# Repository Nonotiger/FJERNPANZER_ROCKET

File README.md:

# FJERNPANZER_ROCKET
This is theoretical design of a rocket produced by FJERNPANZER. The rocket will be converted into a military applicance, if rocket fuel is acquired.

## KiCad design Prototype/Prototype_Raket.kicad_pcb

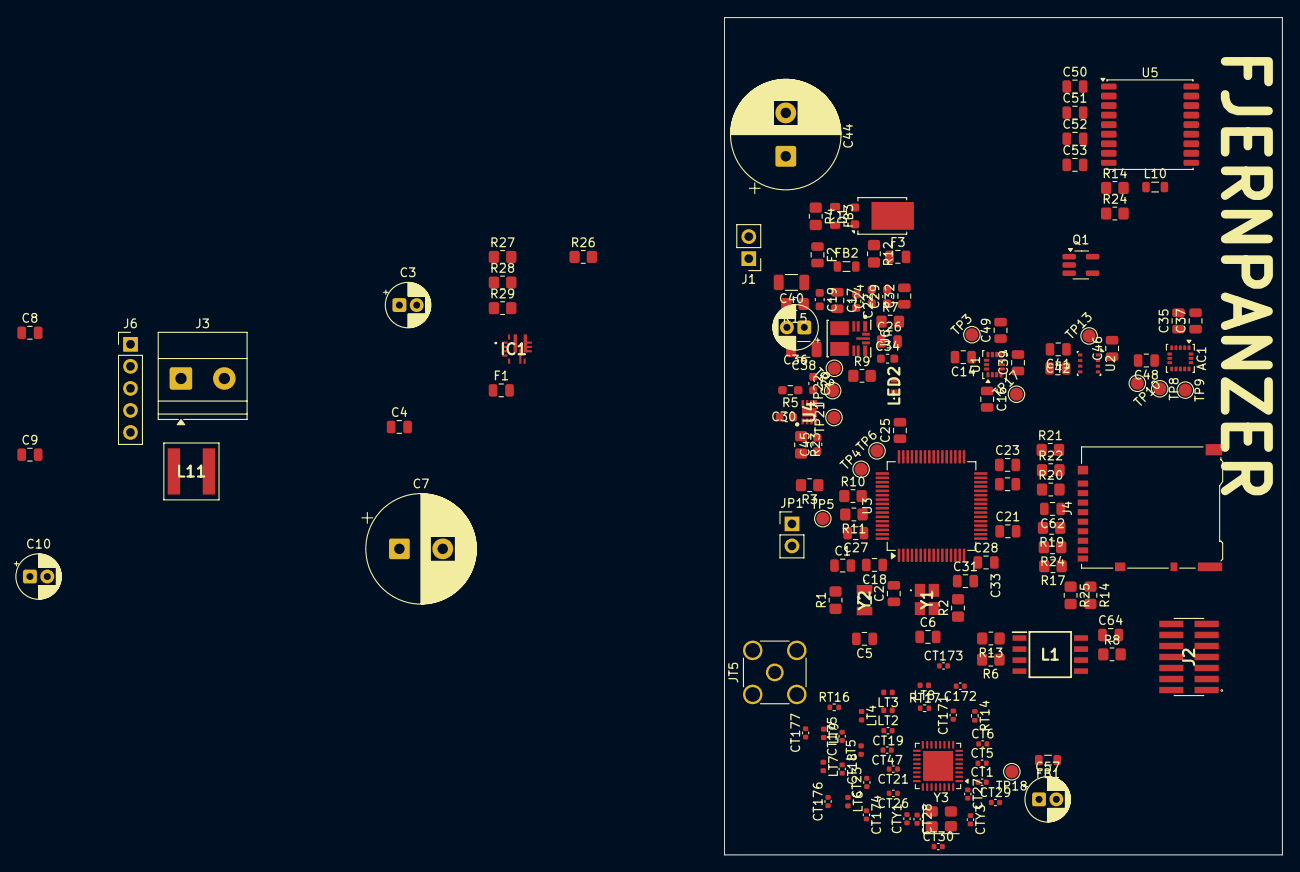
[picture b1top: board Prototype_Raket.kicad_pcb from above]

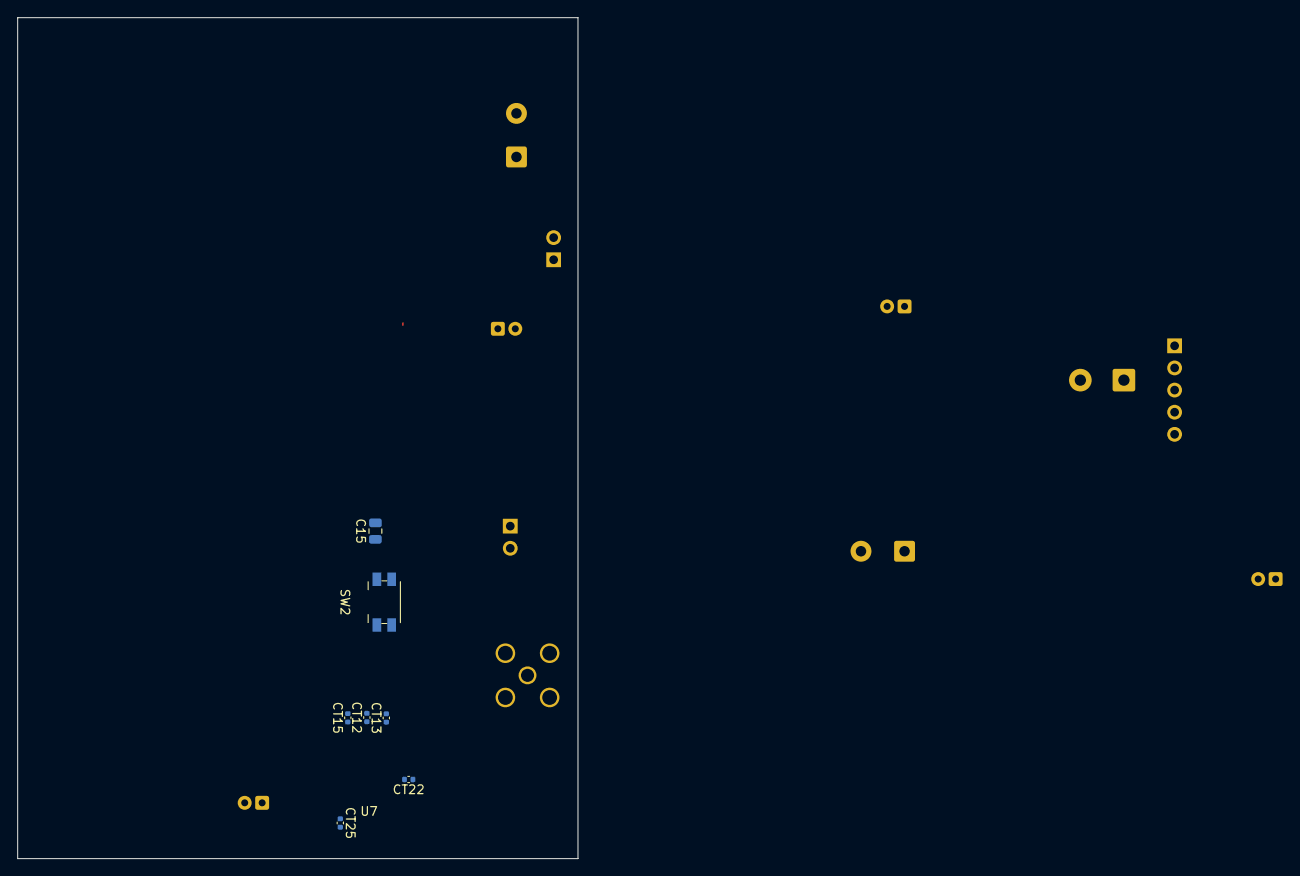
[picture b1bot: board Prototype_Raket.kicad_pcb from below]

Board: 4 copper layers, 64.3 x 96.5 mm, 163 parts (7 on the bottom side), 95 nets.

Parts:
AC1: H3LIS331DLTR; LGA-16_3x3mm_P0.5mm_LayoutBorder3x5y
C1, C5: C_0805_2012Metric
C2, C6: 16p; C_0805_2012Metric
C3: 15uF; CP_Radial_D5.0mm_P2.00mm
C4, C8, C62, C64: 100nF; C_0805_2012Metric
C7, C44: 1000uF; CP_Radial_D12.5mm_P5.00mm
C9: 100pF; C_0805_2012Metric
C10, C57: 47uF; CP_Radial_D5.0mm_P2.00mm
C14, C15, C16, C21, C23, C25, C27, C32, C37, C39, C41, C42, C46, C48, C49, C50, C51, C52, C53: 100n; C_0805_2012Metric
C17: 10u; C_0805_2012Metric
C18, C33: 4u7; C_0805_2012Metric
C19, C20, C30, C45: 100n; C_0603_1608Metric
C22, C24: 2u2; C_0603_1608Metric
C26: 100u; C_0805_2012Metric
C28: 1u; C_0805_2012Metric
C29: 4u7; C_0603_1608Metric
C31: 10n; C_0805_2012Metric
C34: 1u; C_0603_1608Metric
C35: 10uF; C_0805_2012Metric
C36: 22u; CP_Radial_D5.0mm_P2.00mm
C38, C40: 22u; C_1206_3216Metric
C172: 100pF; C_0402_1005Metric
CT1, CT5, CT12, CT13, CT15, CT22, CT25, CT26, CT27, CT28, CT29: 47nF; C_0402_1005Metric
CT6: 220nF; C_0402_1005Metric
CT18: 2.2pF; C_0402_1005Metric
CT19, CT47: 3.3pF; C_0402_1005Metric
CT21, CT171: 10nF; C_0402_1005Metric
CT23: 1.5nF; C_0402_1005Metric
CT30, CT177: DNM_0402; C_0402_1005Metric
CT173: 33pF; C_0402_1005Metric
CT174: 15pF; C_0402_1005Metric
CT175: 3pF; C_0402_1005Metric
CT176: 1pF; C_0402_1005Metric
CTY1, CTY3: 15pF; C_0402_1005Metric
D1: Not Decided; TO-277B
F1, F2, F3: Not Decided; C_0805_2012Metric
FB1: BLM18KG102BH1D; L_0805_2012Metric
FB2: BMC-Q1J0005H; L_0805_2012Metric
FB3: 600R@100MHz; L_0805_2012Metric
IC1: TPS56637RPAR
J1: Conn_01x02_Pin; PinHeader_1x02_P2.54mm_Vertical
J2: FTSH-107-01-F-DV-K; FTSH-107-XX-YYY-DV-K
J3: Conn_01x02_Pin; TerminalBlock_Phoenix_MKDS-1,5-2_1x02_P5.00mm_Horizontal
J4: Micro_SD_Card_Det_Hirose_DM3AT; microSD_HC_Hirose_DM3AT-SF-PEJM5
J6: Conn_01x05_Pin; PinHeader_1x05_P2.54mm_Vertical
JP1: Jumper_2_Small_Open; PinHeader_1x02_P2.54mm_Vertical
JT5: W5017; SMA_Amphenol_132291_Vertical
L1: W25Q128JVSIQ_TR; SOIC127P780X195-8N
L10: L_Small; L_0805_2012Metric
L11: 5.6uH, 14.5mOhm; XAL6060562MEC
LED2: VLMTG1400-GS08; VLMTG1400GS08
LT2: 15nH; L_0402_1005Metric
LT3, LT4, LT5, LT9: 12nH; L_0402_1005Metric
LT6: 7.5nH; L_0402_1005Metric
LT7: 18nH; L_0402_1005Metric
LT8: 10nH; L_0402_1005Metric
Q1: PMOS; SOT-23-5_HandSoldering
R1, R2, R7: 0R; R_0805_2012Metric_Pad1.20x1.40mm_HandSolder
R3, R12, R13, R14, R24#2, R25, R26, R29: 10k; R_0805_2012Metric_Pad1.20x1.40mm_HandSolder
R4: 3.3m; R_0805_2012Metric_Pad1.20x1.40mm_HandSolder
R5: 1k5; R_0603_1608Metric_Pad0.98x0.95mm_HandSolder
R6, R8, R10, R11: 4k7; R_0805_2012Metric_Pad1.20x1.40mm_HandSolder
R9: 510R; R_0805_2012Metric_Pad1.20x1.40mm_HandSolder
R14#2: 56k; R_0805_2012Metric_Pad1.20x1.40mm_HandSolder
R15: 10m; R_0805_2012Metric_Pad1.20x1.40mm_HandSolder
R17, R19, R20, R21, R22: 47k; R_0805_2012Metric_Pad1.20x1.40mm_HandSolder
R23: 1k5; R_0805_2012Metric_Pad1.20x1.40mm_HandSolder
R24: 10; R_0805_2012Metric_Pad1.20x1.40mm_HandSolder
R27: 20k; R_0805_2012Metric_Pad1.20x1.40mm_HandSolder
R28: 73k; R_0805_2012Metric_Pad1.20x1.40mm_HandSolder
RT14: 56k; R_0402_1005Metric
RT16: 10m; R_0402_1005Metric
RT17: 10; R_0402_1005Metric
SW2: SW_Push; Panasonic_EVQPUJ_EVQPUA
TP2, TP3, TP4, TP5, TP6, TP8, TP9, TP10, TP13, TP17, TP18, TP21, TP22: TestPoint; TestPoint_Pad_D1.5mm
U1: ISM330DLC; LGA-14_3x2.5mm_P0.5mm_LayoutBorder3x4y
U2: BME280; Bosch_LGA-8_2.5x2.5mm_P0.65mm_ClockwisePinNumbering
U3: STM32F446RETx; LQFP-64_10x10mm_P0.5mm
U4: INA2180A3IDSGR; SON50P200X200X80-9N
U5: MAX-M10S; ublox_MAX
U6: TPSM33620S3QRDNRQ1
U7: CC1200; QFN-32-1EP_5x5mm_P0.5mm_EP3.45x3.45mm
Y1: FL2400135Z
Y2: SC32A-9PF10PPM; SC32A9PF10PPM
Y3: CS03880-40M; Crystal_SMD_3225-4Pin_3.2x2.5mm

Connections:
+3.3V: AC1.1 (VDD_IO), AC1.7 (SDO_SA0), AC1.8 (CS), AC1.14 (VDD), AC1.15 (RESERVED_2), C14.1, C16.1, C18.1, C20.2, C21.1, C23.1, C25.1, C27.1, C28.1, C31.1, C35.1, C37.1, C39.1, C40.1, C41.1, C42.1, C46.1, C48.1, C49.1, C50.1, C51.1, C62.1, C64.1, FB1.1, J4.4 (VDD), JP1.2 (B), L1.8 (VCC), Q1.2 (G), Q1.3 (S), R6.2, R8.2, R9.1, R10.1, R11.2, R12.1, R13.2, R14.2, R15.2, R17.2, R19.2, R20.1, R21.1, R22.1, R24#2.2, R25.2, R26.1, TP3.1 (1_1), TP6.1 (1_1), TP10.1 (1_1), TP13.1 (1_1), U1.1 (SDO/SA0), U1.5 (VDDIO), U1.8 (VDD), U1.12 (CS), U2.2 (CSB), U2.6 (VDDIO), U2.8 (VDD), U3.1 (VBAT), U3.13 (VDDA), U3.19 (VDD), U3.32 (VDD), U3.48 (VDD), U3.64 (VDD), U4.6 (IN-2), U4.8 (VS), U5.7 (VCC_IO), U5.8 (VCC)
+3.3V_TLM: C57.1, C172.2, CT1.1, CT5.1, CT12.1, CT13.1, CT15.1, CT22.1, CT25.1, CT27.1, CT28.1, CT171.2, CT173.2, FB1.2, RT17.2, U7.1 (VDD_GUARD), U7.5 (DVDD), U7.12 (DVDD), U7.13 (AVDD_IF), U7.15 (AVDD_RF), U7.22 (AVDD_SYNTH1), U7.25 (AVDD_PFD_CHP), U7.27 (AVDD_SYNTH2), U7.28 (AVDD_XOSC)
/Debugging/T_NRST: C15.1, J2.12, SW2.1, U3.7 (NRST)
/Debugging/T_SWCLK: J2.6, U3.49 (PA14)
/Debugging/T_SWDIO: J2.4, U3.46 (PA13)
/Debugging/T_SWO: J2.8, U3.55 (PB3)
/Debugging/T_VCP_RX: J2.13, U3.17 (PA3)
/Debugging/T_VCP_TX: J2.14, U3.16 (PA2)
/MCU/3V3_PGOOD: R12.2, U3.56 (PB4), U6.1 (PGOOD)
/MCU/3V3_sense: C30.1, R5.2, U3.10 (PC2)
/MCU/+BAT_Sense: C45.1, R23.2, U3.15 (PA1)
/MCU/CS_FLASH: L1.1 (/CS), R13.1, U3.20 (PA4)
/MCU/INT0_TLM: U3.37 (PC6), U7.10 (GPIO0)
/MCU/INT1_ACC: AC1.11 (INT1), TP9.1 (1_1), U3.24 (PC4)
/MCU/INT1_IMU: TP17.1 (1_1), U1.4 (INT1), U3.8 (PC0)
/MCU/INT2_ACC: AC1.9 (INT2), TP8.1 (1_1), U3.25 (PC5)
/MCU/INT2_IMU: U1.9 (INT2), U3.9 (PC1)
/MCU/INT2_TLM: U3.38 (PC7), U7.4 (GPIO2)
/MCU/OSC32_IN: C1.2, U3.3 (PC14), Y2.1
/MCU/OSC32_OUT: R1.2, U3.4 (PC15)
/MCU/OSC_IN: C2.2, U3.5 (PH0), Y1.1
/MCU/OSC_OUT: R2.2, U3.6 (PH1)
/MCU/PWM_S1: J6.1, U3.41 (PA8)
/MCU/PWM_S2: J6.2, U3.42 (PA9)
/MCU/PWM_S3: J6.3, U3.43 (PA10)
/MCU/PWM_S4: J6.4, U3.44 (PA11)
/MCU/SCL_I2C1: AC1.4 (SCL_SPC), R10.2, TP4.1 (1_1), U1.13 (SCL), U2.4 (SCK), U3.58 (PB6)
/MCU/SDA_I2C1: AC1.6 (SDA_SDI_SDO), R11.1, TP5.1 (1_1), U1.14 (SDA), U2.3 (SDI), U3.59 (PB7)
/MCU/SDIO_CLK: J4.5 (CLK), U3.53 (PC12)
/MCU/SDIO_CMD: J4.3 (CMD), R20.2, U3.54 (PD2)
/MCU/SDIO_D0: J4.7 (DAT0), R19.1, R24#2.1, U3.39 (PC8)
/MCU/SDIO_D1: J4.8 (DAT1), R17.1, U3.40 (PC9)
/MCU/SDIO_D2: J4.1 (DAT2), R21.2, U3.51 (PC10)
/MCU/SDIO_D3: J4.2 (DAT3/CD), R22.2, U3.52 (PC11)
/MCU/SD_CARD_DETECT: J4.9 (DET_B), R14.1, R25.1, U3.14 (PA0)
/MCU/SPI1_MISO_FLASH: L1.2 (DO_(IO1)), U3.22 (PA6)
/MCU/SPI1_MOSI_FLASH: L1.5 (DI_(IO0)), U3.23 (PA7)
/MCU/SPI1_SCK_FLASH: L1.6 (CLK), U3.21 (PA5)
/MCU/SPI2_CS_TLM: U3.33 (PB12), U7.11 (~CS)
/MCU/SPI2_MISO_TLM: U3.35 (PB14), U7.9 (SO(GPIO1))
/MCU/SPI2_MOSI_TLM: U3.36 (PB15), U7.7 (SI)
/MCU/SPI2_RESET_TLM: U3.28 (PB2), U7.2 (~RESET)
/MCU/SPI2_SCLK_TLM: U3.34 (PB13), U7.8 (SCLK)
/MotorPCB/SERVO_PGOOD: IC1.4 (PG), J6.5, R26.2, U3.45 (PA12)
/Power/+BAT_Raw: J1.1, Q1.1 (D), R4.1, TP22.1 (1_1), U4.3 (IN+1)
/Power/+Shunt_+3V3: C36.1, C38.1, R15.1, TP2.1 (1_1), U4.5 (IN+2), U6.4 (VOUT), U6.9 (FB)
/Power/+VCC_Shunt: F2.1, FB3.1, R4.2, TP21.1 (1_1), U4.2 (IN-1)
/Power/BATTV_UF: C17.1, C19.1, C44.1, F3.2, FB2.1
/Sensors/GPS_ANT: L10.2, U5.11 (RF_IN)
/Telemetry/LNA_N: CT47.1, LT2.2, LT4.1, U7.20 (LNA_N)
/Telemetry/LNA_P: CT19.1, LT2.1, LT3.1, U7.19 (LNA_P)
/Telemetry/PA: CT174.1, LT8.2, U7.17 (PA)
/Telemetry/TRX_SW: CT18.1, LT5.1, U7.18 (TRX_SW)
Control_V+: C10.2, F2.2, L11.2, R27.2, R29.2
GND: AC1.5 (GND_1), AC1.10 (RESERVED_1), AC1.12 (GND_2), AC1.13 (GND_3), AC1.16 (GND_4), C1.1, C2.1, C3.2, C4.2, C5.1, C6.1, C7.2, C10.1, C14.2, C15.2, C16.2, C17.2, C18.2, C19.2, C20.1, C21.2, C22.2, C23.2, C24.2, C25.2, C26.2, C27.2, C28.2, C29.2, C30.2, C31.2, C32.2, C33.2, C34.2, C35.2, C36.2, C37.2, C38.2, C39.2, C40.2, C41.2, C42.2, C44.2, C45.2, C46.2, C48.2, C50.2, C51.2, C52.2, C53.2, C57.2, C62.2, C64.2, C172.1, CT1.2, CT5.2, CT6.2, CT12.2, CT13.2, CT15.2, CT21.2, CT22.2, CT25.2, CT26.2, CT27.2, CT28.2, CT29.2, CT30.2, CT47.2, CT171.1, CT175.2, CTY1.2, CTY3.2, IC1.3 (AGND), IC1.9 (PGND), IC1.10 (MODE), J1.2, J2.5, J2.7, J2.11, J3.2, J4.6 (VSS), J4.10 (DET_A), J4.SH (SHIELD), JT5.2 (Ext), L1.4 (GND), LED2.1 (K), LT3.2, R3.2, R28.1, RT14.1, SW2.2, U1.2 (SDx), U1.3 (SCx), U1.6 (GND), U1.7 (GND), U2.1 (GND), U2.5 (SDO), U2.7 (GND), U3.12 (VSSA), U3.18 (VSS), U3.31 (VSS), U3.47 (VSS), U3.63 (VSS), U4.4 (GND), U4.9 (EP), U5.1 (GND), U5.10 (GND), U5.12 (GND), U6.10 (GND), U6.11 (MODE/SYNC), U7.32 (EXT_XOSC), U7.33 (GND_EP), Y1.2, Y1.4, Y3.2 (G), Y3.4 (G)
unnamed: C5.2, R1.1, Y2.2
unnamed: C6.2, R2.1, Y1.3
unnamed: C9.2, R27.1
unnamed: C26.1, R7.2
unnamed: C53.1, L10.1, R24.2
unnamed: CT19.2, LT4.2, LT5.2
unnamed: CT173.1, LT8.1, RT17.1
unnamed: CT174.2, CT176.1, LT6.2
unnamed: CT175.1, CT177.1, LT7.1, LT9.2
unnamed: CT18.2, CT176.2, LT6.1, LT7.2
unnamed: CT177.2, LT9.1, RT16.1
unnamed: D1.1 (A), D1.2 (A), FB3.2
unnamed: D1.3 (K), F3.1
unnamed: C8.2, IC1.7 (BOOT)
unnamed: C9.1, IC1.2 (FB), R28.2, R29.1
unnamed: C8.1, IC1.6 (SW), L11.1
unnamed: F1.1, J3.1
unnamed: JP1.1 (A), R3.1, U3.60 (BOOT0)
unnamed: JT5.1 (In), RT16.2
unnamed: L1.3 (IO2), R6.1
unnamed: L1.7 (IO), R8.1
unnamed: LED2.2 (A), R9.2
unnamed: C33.1, U3.30 (VCAP_1)
unnamed: R23.1, U4.1 (OUT1)
unnamed: R5.1, U4.7 (OUT2)
unnamed: R24.1, U5.14 (VCC_RF)
unnamed: C52.1, R14#2.2, U5.6 (V_BCKP)
unnamed: C22.1, C24.1, C29.1, C32.1, FB2.2, R7.1, U6.2 (EN), U6.3 (VIN)
unnamed: C34.1, U6.8 (VCC)
unnamed: CT6.1, U7.6 (DCPL)
unnamed: CT26.1, U7.26 (DCPL_PFD_CHP)
unnamed: CT21.1, U7.21 (DCPL_VCO)
unnamed: CT29.1, U7.29 (DCPL_XOSC)
unnamed: TP18.1 (1_1), U7.3 (GPIO3)
unnamed: CT23.2, U7.23 (LPF0)
unnamed: CT23.1, U7.24 (LPF1)
unnamed: RT14.2, U7.14 (RBIAS)
unnamed: CT30.1, CTY1.1, U7.30 (XOSC_Q1), Y3.1
unnamed: CTY3.1, U7.31 (XOSC_Q2), Y3.3
ServoVCC: C3.1, C4.1, C7.1, F1.2, IC1.8 (VIN_1)
